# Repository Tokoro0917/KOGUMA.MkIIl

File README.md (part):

# KOGUMA MkIIl

STM32F446RE をベースにしたマイクロマウス(クラシック、迷路探索ロボット)のファームウェア。

- 大会までの予定とやることは`TODO.md`
- 詳しい設計・調べたこと・変更の記録は`docs/`(下の「資料」)

## 目次

1. [動かし方](#動かし方)
2. [大会での流れ](#大会での流れ)
3. [モード](#モード)
4. [出力とビューア](#出力とビューア)
5. [よく変える設定](#よく変える設定)
6. [実機での確認状況](#実機での確認状況)
7. [壁センサ・横壁制御・壁切れ](#壁センサ横壁制御壁切れ)
8. [テストとCI](#テストとci)
9. [ビルド・ハードウェア・ディレクトリ](#ビルドハードウェアディレクトリ)
10. [資料](#資料)

## 動かし方

ロータリーエンコーダの`Encorder_mode_out()`(モード)と`Encorder_number_out()`(ナンバー)の組み合わせで動作を選ぶ。どちらも0〜15。

1. モードとナンバーを選ぶ
2. **左前センサに手をかざす**(`Sensor_Enter()`、FLが1400超)
3. ブザーのあと**左右の横センサに手をかざす**(`Sensor_Start()`、L+Rが2000超)とスタート

走行が終わると`Encorder_count_reset()`でモード0・No.0に戻る。迷路とログはRAMにしか残らないので、**出力するまで電源を切らない**。

## 大会での流れ

大会の日はコードを変えず、感度合わせの値だけ変える(2026-11-21 全日本学生大会の時点)。

1. **ゴールを確かめる**: `Core/Inc/Define.h` の `MAZE_GOOL_X/Y` が `(MAZE_SIZE / 2 - 1)` になっているか(ベンチテストで書き換えたままだとゴールに行けない)
2. **電池**: 満充電で、走る前の電圧が 15.8V 以上
3. **会場に着いたら感度合わせ**(モード3 No.5): 区画中心で値を測る → 出た行(`WallDist_Scale`と各しきい値)を書き写す → ビルドし直して書き込む(手順は「会場ごとの感度合わせ」)。書き込むだけなら STM32CubeIDE の Run(緑の▶)
4. **動作確認**: モード4 No.0(センサ表示)で壁のあり・なし。試走できれば探索して、出力(モード4 No.7)で迷路を見る
5. **探索 → 最短**: モード0 **No.10**(未知壁探索 → スタートに戻る → 2000 の最短)。最短を何回も走れるなら **No.11**(最短4回、最後にスタートへ戻る)。どちらも 2026-11-10 に実機で確認
6. **最短だけ走らせ直す**: モード1 **No.5**(ダイクストラ、コーナー2000、柱の壁切れ。2026-10-25 の九州地区大会で 2.982 秒、優勝)。2400 は V90 を直していないので使わない
7. 走らせるたびに、電源を切らずに出力(モード4 No.7)し、ビューアで保存する(迷路とログはRAMにしか残らない。リセットや電源断で消える)

気をつけること:

- `Core/Inc/Define.h`の`MAZE_GOOL_X/Y`は標準ゴール(迷路中央2×2、`MAZE_SIZE/2-1`)。ベンチテストでスタート近くにゴールを置きたいときだけ一時的に書き換え、**書き換えたままコミットしないこと。** 行き止まり潰しのゴール保護もこの定数から導出している。出力(モード4 No.7)の迷路の図の`G`でゴールの位置を確認できる。
- `Move.c`の`Short_Dijkstra_Move2000()`終端の旋回角度(180°→270°)の調整は、手元で作業中ならリポジトリには未反映。
- **フェイルセーフで止まったとき**(2026-10-27 から、ToraNeko.Mk3 と同じ戻り方): モーターと吸引が止まり、LED が全部 0.5 秒ごとに点滅する。**スイッチ(基板の S2)を押す**と、「ロード中」(LED1〜8 を順に点ける、約1秒)を出してモード0・No.0 に戻る。電源は切らなくてよい。探索中なら、最後に壁を書いた5区画を書く前の状態に戻して保存してあるので、そのまま探索のやり直しや最短走行ができる
- ゴールは1マス(`MAZE_GOOL_X/Y`、16×16で(7,7))を目指して探索する。標準の中央2×2のゴールなら必ず入れるが、そのマスに行けない迷路では探索の逃げ道がなく、前の壁に向かって進んでしまう(全面探索には「どこにも行けなければスタートへ戻る」逃げ道がある)。

## モード

| モード | 内容 | 番号 |
|---|---|---|
| 0 | **大会用: 探索走行**(往復・片道・全面探索・未知壁探索・探索後の最短・最短4回) | No.1〜12 |
| 1 | **最短走行**(BFS / ダイクストラ、コーナー2000・2400・ターンごと。No.12・13は壁切れを従来で。No.14 はきついターン2000・ゆるいターン2400) | No.1〜14 |
| 2 | サーキット(未実装) | |
| 3 | デバッグ: 固定速度の最短(No.1〜3)、距離の表を作る(No.4)、会場ごとの感度合わせ(No.5)、壁切れのテスト(No.6〜9)、吸引のときのセンサのノイズ(No.10) | No.1〜10 |
| 4 | 基本調整: センサ表示、直進、旋回、**出力(No.7)**、最初のターンの調整など | No.0〜14 |
| 5〜9 | 速度別のターン単体テスト(1.0 / 2.0 / 2.4 / 2.7 / 3.0 m/s) | No.0〜7 |
| 10 | ターンごとの通過速度のターン単体テスト | No.1〜7 |

表にない番号(モード0 No.0・No.13〜15、モード1 No.0・No.14〜15、モード2、モード3 No.0・No.11〜15、モード4 No.15、モード10 No.0・No.8〜15、モード11 No.0・No.8〜15、モード12〜15など)は何もしない。

### モード0: 大会用(探索走行)

往路(スタート→ゴール)のあと、片道ならゴールで止まり、それ以外はスタートへ戻る。区間の終わりごとに`Maze_Save()`する。No.8〜10はスタートに戻ったあと2秒待って最短走行(モード1 No.5と同じ: ダイクストラ、コーナー2000、直線6000mm/s、加速20000)まで走る。中身は`main.c`の`Maze_Search(flags)`で、番号ごとに`SEARCH_*`の組み合わせを指定している。

| No | 走り方 | 復路 | `SEARCH_*` |
|---|---|---|---|
| 0 | (何もしない) | | |
| 1 | スラローム探索(500mm/s、吸引なし) | 往復 | `SLALOM` |
| 2 | スラローム探索 | 往復、復路で**エセ全面探索** | `SLALOM \| ALL` |
| 3 | スラローム探索 | **片道**(ゴールで止まる) | `SLALOM \| ONEWAY` |
| 4 | 吸引探索(1000mm/s、吸引あり) | 往復 | `SUCTION` |
| 5 | 吸引探索 | 往復、復路で**エセ全面探索** | `SUCTION \| ALL` |
| 6 | 吸引探索 | ゴール後に**ダイクストラ誘導の未知壁探索**、終わったらスタートへ | `SUCTION \| DIJKSTRA` |
| 7 | 吸引探索+**既知区間加速** | No.6と同じ | `SUCTION \| DIJKSTRA \| KNOWN` |
| 8 | スラローム探索 | 往復 → **最短** | `SLALOM \| SHORTEST` |
| 9 | 吸引探索 | 往復 → **最短** | `SUCTION \| SHORTEST` |
| 10 | 吸引探索+**既知区間加速** | No.6と同じ → **最短** | `SUCTION \| DIJKSTRA \| KNOWN \| SHORTEST` |
| 11 | 吸引探索+**既知区間加速** | No.10 の最短を**4回**。最短のあとは、ゴールから No.6 と同じ探索をしながらスタートへ帰り、2秒待って次の最短。4回目のあともスタートへ帰り、帰れたら曲を流す(自律賞の条件) | `SUCTION \| DIJKSTRA \| KNOWN \| SHORTEST \| REPEAT` |
| 12 | 吸引探索+**既知区間を斜めで**(お遊び、ブランチ `claude/play-known-naname`) | No.10 と同じで、既知区間を斜めの命令列(`Known_Pass_NANAME`)で走る。斜め入り・斜め出・V90 は `G_Turn1000`(モード5で調整)、斜めの直線は最大3000・加速度10000 | `SUCTION \| DIJKSTRA \| KNOWN \| KNOWN_NANAME \| SHORTEST` |

片道(No.3)はゴール区画に入ったところで、Uターンのときと同じ減速(70mm)で止まる。

No.11(2026-10-20)は、最短走行のあと、止まった区画と向きを命令列から求め(`Maze.c`の`Short_Pass_End_Cell()`。ゴールに入った区画の1つ奥の区画の中心で、最後に180°向きを変えている)、そこからスタートへ帰る(`main.c`の`Maze_Return_From_Goal()`)。帰りは、保存した迷路に戻してから(最短走行は見ていない壁を壁で埋めるため)、ダイクストラ誘導の未知壁探索をして、見る壁がなくなったらスタートへ帰る。止まった区画のほかの壁は見ていないことがあるので、最初は来た区画へまっすぐ出る。最短がゴールまで走れなかったときや、帰る途中でフェイルセーフが働いたときは、そこでやめる。走行ログ・壁切れのログは、最後に走った最短のものが残る。

既知区間加速(`Robot_Maze_Pass_Action()`)は、次の区画が探索済みなら、未探索の区画の手前までを`Known_Pass_Generation()`でまとめて経路にし、直線を最大4000mm/sで走る。

ダイクストラ誘導(No.6/No.7/No.10)は往路でゴールに着いたあと、スタート→ゴールのダイクストラ経路上に残っている未確認の壁を、今いる位置から直接見に行く(`Maze_Unknown_Wall_Scan()`)。経路の計算は、未確認の壁を「通れる」として行う。計算し直すのは、ゴールに着いた直後、Uターンしたとき、**見に行った壁が実際にあった・経路のほかの壁が「壁あり」とわかった(経路がふさがれた)とき**、**見に行く途中で目標の区画に行けなくなったとき**(2026-10-27)だけで、どれも**機体が区画の中央で止まっているあいだに**計算する。ゴールに着いた直後と、壁があったときは、次の区画の中央で止まり、前に壁があれば壁合わせをしてから計算し、進む向きを決めて発進する(`Robot_Maze_Stop_And_Go()`)。Uターンでは止まっているあいだに計算し(`G_Stop_Hook`)、行き止まりでなければ計算した結果で進む向きを決め直す。見に行った壁がなかった(通れた)ときは、ダイクストラは計算し直さず、止まらずに同じ経路で次の未確認の壁を探す。経路上の未知壁がなくなったらスタートへ帰る。このとき、その経路の壁はすべて確認済みなので、それが本当の最短経路になる。経路は、よく使う最短走行の値の組(`ShortParam.c` の `G_Short_Run_Set`。今は 2000 と 2400)ごとに、それぞれの時間で一番速いものを求め、全部の組の経路の壁を確認する(2026-10-27。1つ目の組の経路を見終わったら、止まって次の組の経路を計算する)。なので、どの組で最短を走っても本当の最短経路になる。

エセ全面探索(`Maze_Unkown_ALL_ModeSet()`)が有効なのは**No.2・No.5だけ**。したがって**行き止まり潰しが走行に影響するのもこの2つだけ**(`Maze_DeadEnd_Fill()`自体は常に計算されるが、結果を使う`Maze_Gool_Setting()`の分岐がALL_MODE時にしか通らないため)。

探索のアルゴリズム(BFS・ダイクストラ、行き止まり潰し)は`docs/maze_algorithm.md`。

### モード1: 最短走行

`Short_*_Move*(MAX, AC)`の`MAX`が直線区間の最高速度、`AC`が加速度。関数名の数字はコーナー通過速度。直線最高速はどれも6000mm/s。中身は`main.c`の`Maze_Shortest_Run()`。斜めの直線の加速度は番号ごとの`ac_nn`(`G_Short_AC_NANAME`)で決める。

| No | 経路生成 | コーナー | 加速度 | 斜めの加速度 | 関数 |
|---|---|---|---|---|---|
| 0 | (何もしない) | | | | |
| 1 | BFS | 2000 | 15000 | 10000 | `Short_NANAME_Move2000` |
| 2 | BFS | 2000 | 20000 | 15000 | `Short_NANAME_Move2000` |
| 3 | BFS | 2400 | 20000 | 15000 | `Short_NANAME_Move2400` |
| 4 | ダイクストラ | 2000 | 15000 | 10000 | `Short_Dijkstra_Move2000` |
| 5 | ダイクストラ | 2000 | 20000 | 15000 | `Short_Dijkstra_Move2000` |
| 6 | ダイクストラ | 2000 | 23000 | 18000 | `Short_Dijkstra_Move2000` |
| 7 | ダイクストラ | 2000 | 25000 | 20000 | `Short_Dijkstra_Move2000` |
| 8 | ダイクストラ | 2400 | 20000 | 15000 | `Short_Dijkstra_Move2400` |
| 9 | ダイクストラ | 2400 | 23000 | 18000 | `Short_Dijkstra_Move2400` |
| 10 | BFS | ターンごと(`docs/turnv_design.md`) | 20000 | 15000 | `Short_NANAME_MoveTurnV` |
| 11 | ダイクストラ | ターンごと(`docs/turnv_design.md`) | 20000 | 15000 | `Short_Dijkstra_MoveTurnV` |
| 12 | ダイクストラ | 2400(No.8と同じ。**壁切れは従来**、柱と比べる用) | 20000 | 15000 | `Short_Dijkstra_Move2400` |
| 13 | ダイクストラ | 2000(No.5と同じ。**壁切れは従来**、柱と比べる用) | 20000 | 15000 | `Short_Dijkstra_Move2000` |
| 14 | ダイクストラ(経路は No.5 と同じ) | **きついターン(斜め入り45・135、斜め出135、V90)は 2000(`G_Turn2000`)、ゆるいターン(大回り90・大回り180・斜め出45)は 2400(`G_Turn2400`)**。どちらも合わせてある値をそのまま使う。直線を挟まずにつながるターンは 2000 にそろえる。吸引70(2400 と同じ)。2026-11-21、実機では未確認 | 20000 | 15000 | `Short_Dijkstra_MoveMix` |

`main.c`の`Short_WallCut_Pillar`を1にすると、最短走行(モード1、モード0 No.8〜10の探索後の最短)の壁切れを柱で見る(「壁切れ」)。既定は1(2026-10-18 から。0 で従来に戻る)。

No.10・No.11(ターンごとの通過速度)の考え方と速度の決め方は`docs/turnv_design.md`。

No.2とNo.5はパラメータが同一で、BFS経路とダイクストラ経路の比較用になっている。

`Short_Dijkstra_Move2400`は、経路の作り方だけをダイクストラに切り替えて`Short_NANAME_Move2400`と同じ動きで走る(命令列の形はBFSと同じ)。`Short_Dijkstra_Move2000`は旋回のパラメータが`Short_NANAME_Move2000`とは別に調整されている。

コーナー2700(`Short_NANAME_Move2700`)の関数は残してあるが、今はどの番号からも呼んでいない(実機で走れていない)。

### モード3: デバッグ

直線最高速をコーナー速度と同値にして、区間ごとの加減速を実質なくしたもの。

| No | コーナー | 直線最高速 | 加速度 |
|---|---|---|---|
| 1 | 2000 | 2000 | 20000 |
| 2 | 2400 | 2400 | 20000 |
| 3 | 2700 | 2700 | 20000 |
| 4 | 壁センサの距離の表を作る(「距離の表を作り直すとき」) | | |
| 5 | 会場ごとの感度合わせ(区画中心、「会場ごとの感度合わせ」) | | |
| 6〜9 | 壁切れの位置のテスト(500 / 1000 / 2000 / 2400。「壁切れ」、結果は出力 モード4 No.7) | | |
| 10 | 吸引のときのセンサのノイズ(止まったまま約15秒。`docs/sensor_noise.md`) | | |

### モード4: 基本調整

| No | 内容 |
|---|---|
| 0 | センサ値・電圧・ジャイロのprintf表示 |
| 1 | 直進テスト(タイヤ径の測定用。吸引35(探索と同じ、2026-10-21 から。それまでは70)、最大1000・加速度5000で1080mm。タイヤ径 = 今の値 × 実際の距離 / 走行ログの最後の x(1080 より少し手前で止まるので、1080 で割らない)) |
| 2 | その場180°旋回テスト |
| 3 | スラロームテスト |
| 4 | 斜め走行テスト |
| 5 | 吸引ON(duty 90)。左前センサに手をかざすと止まる |
| 6 | 壁合わせ |
| 7 | **出力**。RAMに残っているデータを全部出す(迷路、壁切れのログ、走行ログ。下の「出力とビューア」) |
| 8 | No.1と同じ直進テスト(吸引70、最大1000・加速度5000で1440mm)を、横壁制御のセンサ値版(`Kp`/`Kd`)で走る。距離版との比較・切り戻し用 |
| 9 | 最短走行の最初のターンの調整: 右大回り90を1480で(スタート位置から、ターン後は2400へ加速して1区画で止まる) |
| 10 | 同 右斜め入り45を1110で(ターン後は斜めに2区間で止まる) |
| 11 | 同 右斜め入り135を1400で |
| 12〜14 | No.9〜11 と同じターンを、加速しながら曲がる方式で(`G_First_Turn_Accel = 1`) |

### モード5〜9: 速度別のターン単体テスト

モード5=1.0, 6=2.0, 7=2.4, 8=2.7, 9=3.0 m/s。No.1〜7は共通で 1=90°, 2=180°, 3=in45°, 4=in135°, 5=out45°, 6=out135°, 7=V90°。

| モード | No.0 | No.1〜7 |
|---|---|---|
| 5 (1.0m/s) | 90°小回り(吸引探索の小回り) | 1000のターン単体(`G_Turn1000`、左旋回、壁切れなし。吸引35。置き方は2000と同じ。吸引探索の既知区間の斜め(モード0 No.12)と同じ値。2026-10-21) |
| 6 (2.0m/s) | 直進(吸引51、最大6000・加速度40000で1080mm) | 2000のターン単体(`G_Turn2000`、左旋回、壁切れなし。最短の2000と同じ値) |
| 7 (2.4m/s) | 空 | 2400のターン単体(`G_Turn2400`、左旋回、壁切れなし。最短の2400と同じ値。2026-10-21 から1つずつ単体で走る。斜めから入るターンは斜め3区間で加速するので、2000より斜め2区間ぶん後ろに置く) |
| 8 (2.7m/s) | 空 | 実装済み |
| 9 (3.0m/s) | 空 | **No.1のみ実装**、2〜7は空 |

「空」はセンサ待機だけで何も走らせない分岐。

### モード11: 2200のターンの停止位置テスト(2026-10-20)

[Turn-Sim_KOGUMA](https://tokoro0917.github.io/Turn-Sim_KOGUMA/)(ターンのシミュレーター)の手順3・6・7の「停止位置テスト」。`Move.c` の `G_Turn2200`(シミュレーターの「Cの表をコピー」をそのまま貼る)の値で、ターンを1つ(左)走り、後ろの直線で減速して止まる(`Turn2200_Test()`)。後ろの直線は、斜めに出るターン(斜め入り45・135、V90)は 254.6mm(斜め2区間、斜めの壁の中点で止まる)、まっすぐ出るターン(大回り、斜め出)は 180mm(次の区画の中心で止まる)。シミュレーターの手順3の「後ろの直線の長さ」にも同じ値を入れる。壁切れは使わず、後距離と後ろの直線は壁制御を切る。吸引70。止まった位置を、理想の停止位置(理想の出口の線上で後ろの直線の長さだけ進んだ点)からのずれ(前後・横)として測り、シミュレーターに入れる。番号はモード6と同じ。

| No | ターン | 置き方 |
|---|---|---|
| 1 | 大回り90 | スタート区画(後ろの壁に当てる)。2区画先の区画の中心まで(24 + 360mm)で加速し、そこから前距離 |
| 2 | 大回り180 | 同上 |
| 3 | 斜め入り45 | 同上 |
| 4 | 斜め入り135 | 同上 |
| 5 | 斜め出45 | 斜めに置く。斜め2区間(254.6mm)で加速し、そこ(斜めの壁の中点)から前距離 |
| 6 | 斜め出135 | 同上 |
| 7 | V90 | 同上 |

### モード10: ターンごとの通過速度のターン単体テスト

`Short_NANAME_MoveTurnV`の`TurnV_Table`の速度とパラメータで、ターンを1つだけ走る(`Move.c`の`TurnV_Test()`、左旋回)。モード7と同じく壁切れを使わず、前距離・後距離は固定の距離で走る。表の`v`や`offset_st`/`offset_end`を変えたら、ここで1つずつ確かめる。

| No | ターン |
|---|---|
| 1 | 大回り90 |
| 2 | 大回り180 |
| 3 | 斜め入り45 |
| 4 | 斜め入り135 |
| 5 | 斜め出45(斜め入り45で斜めに入り、斜めの直線1区間で表の速度に合わせてから) |
| 6 | 斜め出135(同上) |
| 7 | V90(同上) |

## 出力とビューア

### 出力(モード4 No.7)

RAMに残っているデータを全部、迷路 → 壁切れのログ → 走行ログ → センサのノイズ の順に出す(ないものは出さない。最後に`#DONE`)。出力のモードはこれひとつ(感度合わせ・距離の表は、そのモードで出し続ける)。

| データ | いつ残るか | 中身 |
|---|---|---|
| 迷路(`MAZE`) | 探索の区間の終わりごと(`Maze_Save()`) | 壁・見た壁、最短走行の命令列(BFS・ダイクストラ)、計算時間。詳しくは`docs/maze_algorithm.md`の「迷路の出力」 |
| 壁切れのログ(`EDGE`) | 最短走行のあいだ、壁切れのテスト(モード3 No.6〜9) | 柱の端、前距離・後距離の始めと終わり、テストでは1mmごとの横センサの値。詳しくは`docs/pillar_cut_design.md`の付録 |
| 走行ログ(`LOG`) | 最短走行(4msおき・6.4秒、走り始めから)、ターンや直進のテスト(1msおき・1.6秒) | 走った距離、速度、角速度、角度、横の壁までの距離、横壁制御、横センサ、電圧、電池、動作。詳しくは`docs/log_design.md` |
| 探索の直進の壁切れ(`SCUT`) | 探索(モード0)のあいだ、1区画まっすぐ進むたび | 次の境目の推定と距離から予想した位置の差(dc)、直した量、使った側、直前の行動、区画。ビューアで直前の行動ごとの表とグラフにし、書き写す基準のずれを出す。見出しにジャイロのゼロ点(`gyro_ofs`・`gyro_sd`・`gyro_rej`、測るたびの値 `gyro_try`、読み直した回数 `gyro_torn`) |
| 前壁の読み分かれ(`FWALL`) | 探索(モード0)の判断位置で、前の左右のセンサの片方だけが閾値を超えたとき | 行動の番号、区画と向き、前の左右の値、左右の平均で見たら壁ありか。本当の迷路と比べて、`Front_Wall_Map` を決める(`docs/search_stability_research.md` の「段階2を入れた結果」) |
| センサのノイズ(`NOISE`) | モード3 No.10 | 吸引と読み方ごとの、点灯時・消灯時・差のばらつきの表(生の値は測ったそばから出すだけで、ここでは出ない)。`docs/sensor_noise.md` |

### ビューア(`tools/viewer.html`)

ロボットのUART出力を、そのままグラフ・表・迷路にするページ。Tera Termはいらない。ネットも使わない(外から何も読み込まないので、会場でも使える)。

1. ロボットをUSBシリアルでつなぎ、`tools/viewer.html`をWindowsのChrome(かEdge)で開く(ダブルクリック)。Tera Termは閉じておく(同じCOMポートは1つしか開けない)
2. 「接続」を押してCOMポートを選ぶ(115200)。届いた文字は下のコンソールに出る
3. 「保存先フォルダ」でリポジトリの`logs/`を選ぶと、届いたデータを1つずつファイル(`日時_種類.txt`)にして自動で保存する。そのファイルをコミットすれば、Claudeは元のデータをそのまま読める
4. ロボットでモード4 No.7(出力)を選ぶと、残っているデータ(迷路・壁切れ・走行ログ)が全部届き、左の一覧に種類ごとに増えて、自動で表示される

届く途中でデータが抜けると、迷路がまるごと届かなかったり、走行ログの行が足りなくなったりする。2026-10-18 までは、受け取りの入れ物が255バイトしかなく、グラフを描いているあいだにあふれていた(1MBにして、届き終わってから描くようにした)。迷路が届かなかったときはコンソールに、走行ログの行が足りないときはそのログの上に出るので、もう一度出力する。

| ロボットの出力 | 表示 |
|---|---|
| 走行ログ | 速度・角速度・角度・横の壁までの距離・横壁制御(出力・P項・D項)・誤差・使った壁・横センサ・電圧・電池のグラフ。動作(直線・前距離・ターン・後距離・止まる)で背景を色分けする。横軸は時間か走った距離を選べる。ドラッグで拡大(全部のグラフがそろう)、ダブルクリックか Esc か「拡大を元に戻す」ボタンで元に戻す、指すとその時刻の値と動作。表示している範囲の平均・標準偏差・最小・最大の表(動作で絞れる)。一覧で別のログに印を付けると破線で重ねる |
| 壁切れのテスト(モード3 No.6〜9で走らせたあと) | 横センサの値と距離のグラフ(1mmごと。区画の境目と見つけた柱の端を重ねる。柱のところで値がどう下がるか、`Edge_Min_High`をいくつにするかを見る)。左右・種類ごとの c-border(境目の推定 − 区画の境目)の平均・標準偏差。そのページで読んだテスト全部を速度ごとにまとめた表と、c-border と速度の点のグラフ(左右別)、書き写す`Edge_Off`の行 |
| 最短走行の壁切れ | 柱の端・前距離・後距離・従来の壁切れを距離の軸に並べた図。前距離をどれだけ直したか、どの推定を使ったかの表。後距離が X より早く終わったかの表 |
| 迷路 | 迷路の図(見ていない壁は点線)に最短経路を重ねる(青: ダイクストラ。BFS と違うときはオレンジの破線も。区画の境目の真ん中を結んで角を丸めた線なので、斜めは斜めに、大回りは丸く出る。ボタンで区画の中心を結ぶ線にも切り替えられる)。経路の命令列・計算時間 |
| センサのノイズ(モード3 No.10) | 吸引ごとの点灯時・消灯時・差のばらつきの表と見立て(電気か、LEDの点け方か)、読み方ごとの差のばらつきの表、吸引とばらつきのグラフ。測ったそばから受け取ったときは、生の値(1msごと100回)のグラフと、差とPWMの位置の散布図も |
| 探索の直進の壁切れ・前壁の読み分かれ | 直前の行動ごとの dc の表とグラフ、書き写す `Search_Edge_Ref`、ジャイロのゼロ点。前の左右が分かれたところの表(区画・向き・値・平均で見ると) |
| 感度合わせ(モード3 No.5) | 書き写す行(コピーのボタン付き)。測っているあいだ約1秒ごとに届くが、一覧には増やさず、いちばん新しい値に置き換える(5秒あくと新しい測定)。自動では保存しない(残したいときは「ファイルに保存」) |
| センサの値(モード4 No.0、モード3 No.4) | 一覧のいちばん上の「センサの値(そのまま)」。直近10秒を流れるグラフ(FL・L・R・FR、モード4 No.0は電池と角速度、モード3 No.4は表で変換した距離も)と、今の値。「止める」で止めて見られる。直近60秒をCSVで保存できる。モード4 No.0の値は10回の移動平均(`g_sensor_av10`)なので、1回だけの落ち込みは見えにくい |

- 保存したファイルや、Tera Termのログは「ファイルを開く」かドラッグで読み込める(`tools/sample_output.txt`はロボットなしで見た目を確かめる用の例)
- 「ぜんぶ保存」は、ページを開いてから届いた文字を1つのファイルにする(長くなったら最後の約10MB、約14分ぶんだけ)
- 出力の形: どれも`#BEGIN 種類 項目=値 ...`で始まり`#END 種類`で終わる(`LOG`・`EDGE`・`MAZE`・`CENTER`)。`LOG`は次の行が列名なので、列を増やしてもビューアは直さなくてよい
- ダブルクリックで開いた(`file://`)ままで、USBシリアルもフォルダへの保存も使える(Chromiumで確かめた)。もし使えなければ、`tools`で`python -m http.server`を実行して`http://localhost:8000/viewer.html`を開く

## よく変える設定

| 設定 | 場所 | 今の値 | 内容 |
|---|---|---|---|
| `Short_WallCut_Pillar` | `main.c` | 1 | 1で、最短走行の壁切れを柱で見る(「壁切れ」)。0で従来 |
| `Pillar_X_Scale` / `Pillar_X_Offs` / `Pillar_Wait_Ofs` | `motor.c` | 0.5 / −5 / 25 | 柱のとき、前距離の X を X × Scale + Offs に読み替える(X は従来に合わせて調整した値のため)。境目が見つからないときは 区画中心 + 読み替えた X + 25 まで待つ |
| `Search_WallCut` / `Search_Edge_Ref` / `Search_Edge_Win` / `Search_Corr_Max` | `motor.c` | 1 / 0 / 20 / 10 | 探索の1区画の直進の壁切れ(`docs/search_wallcut_design.md`)。0 使わない、**1 記録だけ(走りは今までどおり)**、2 直す。2 のときは、区画の4割を過ぎたら次の境目の柱の端を探し、dc(推定 − 予想)と基準のずれ `Search_Edge_Ref`(記録で測った dc の中央値)の差を ± 10mm まで直す |
| `Side_Align_Enable` / `Side_Too_Close_mm` | `motor.c` | 0 / 64 | 探索の横壁合わせ(2026-11-11、ToraNeko.Mk3 と同じ)。区画の入口で、横壁制御が使っている横の壁が 64mm(区画のまん中は 84mm)より近ければ、**0 記録だけ**、1 その区画のまん中で止まり、近い側へ 90° 回って前壁合わせをし、元の向きに戻ってから発進する(Uターンのときはしない)。回数といちばん近かった距離は、出力(モード4 No.7)の探索の直進の壁切れ(SCUT)の見出しの `side_n`・`side_min`(ビューアでは同じカードに出る) |
| `Front_Wall_Map` / `Front_Wall_Min_Ratio` | `motor.c` / `Wallsensor.c` | 1 / 0.33 | 迷路に書く前壁。0 今までどおり(左右とも閾値を超えたら壁)、**1 記録だけ**(左右が分かれたときを `FWALL` に残す)、2 左右の平均でも壁ありにする(低いほうも閾値 × 0.33 を超えたとき) |
| `Alignment_TIME` / `Align_Min_Time` / `Align_Still_Time` / `Align_Still_V` | `motor.c` | 0.5 / 0.10 / 0.05 / 10 | 止まったときの前壁合わせ。左右の車輪が `Align_Still_V`[mm/s]未満の状態が `Align_Still_Time`[s]続いたら終わる(`Align_Min_Time` より早くは終わらない、上限 `Alignment_TIME`) |
| `Align_Use_mm` / `Kp_FW_mm` / `Kp_FW_dire_mm` | `Wallsensor.c` | 1 / 1.8 / 1.8 | 止まったときの前壁合わせを、感度合わせした距離で行う(前後は左右の平均が84mm、向きは左右の距離の差が0)。0 で今までの生の値(`FlontWall_Distance` 636、`Kp_FW` / `Kp_FW_dire` 0.1) |
| `Gyro_Deadband` | `lsm6dsr.c` | 0.15 | ジャイロのゼロ点を測れたあとの不感帯[dps](まだなら 0.5)。ゼロ点は `Motor_Setup` のたびに 0.3 秒止まって測る(`Gyro_Calibrate`。ばらつき 1.5 dps 超・平均 5 dps 超なら前の値のまま。吸引を回すとばらつき 4〜5 dps なので、吸引の前に測った値を使う) |
| `G_Heading_Keep` | `motor.c` | 1 | 直線から直線へ続けて走るとき、向きの基準(`Gyro_Sigma_error`)を引き継ぐ。ターン・壁合わせ・後退・止まったあとは 0 から。0 で今までどおり(直線の関数を呼ぶたびに 0。2026-10-21) |
| `Pillar_Short_X` | `motor.c` | 5 | 柱のとき、X がこれより小さい前距離(2400の斜め入り)は曲がる側の境目だけを使い、見つからなければ 区画中心 + X(従来と同じ)で曲がる |
| `ac_nn` | `main.c`(モード1の番号ごと) | 上の表 | 最短走行の斜めの直線の加速度(0なら直線の加速度-5000) |
| `G_WallCtrl_Use_mm` | `Wallsensor.c` | 1 | 横壁制御。1=距離版、0=センサ値版 |
| `Kp_mm` / `Kd_mm` | `Wallsensor.c` | 0.30 / 0.06 | 距離版の横壁制御のゲイン(センサ値版の`Kp`=0.05 / `Kd`=0.01と同じ効き) |
| `WallDist_Scale` | `WallDistance.c` | 0.99, 0.96, 1.00, 1.02 | 会場ごとの倍率(FL, R, L, FR)。モード3 No.5で測る |
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
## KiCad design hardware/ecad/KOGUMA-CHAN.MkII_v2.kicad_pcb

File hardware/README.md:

# hardware

機体のハードウェアのデータ。

- `KOGUMA.Mk3.step` — 次の機体 **KOGUMA Mk3** の 3D(機械)。設計の狙いは `docs/next_robot.md`(今の機体 MkIIl のよくない点)
- `ecad/` — **KOGUMA Mk3** の回路図と基板(KiCad)

## KOGUMA.Mk3.step

| | |
|---|---|
| 形式 | STEP (ISO 10303-21), スキーマ AP214 (`AUTOMOTIVE_DESIGN`) |
| 単位 | mm |
| 大きさ | 約21MB / 421,590行(git 内では約3MB) |
| 書き出し | Autodesk Translation Framework v15.17 経由(ST-DEVELOPER v20.2) |
| 書き出し日 | 2026-11-24 |

アセンブリ一式(部品ごとに分かれている)。ヘッダの author / organization は空。

### 開き方

- **FreeCAD**(無料): File → Open でそのまま開く
- **Fusion 360**: アップロード → STEP として挿入
- 見るだけなら [3D Viewer](https://3dviewer.net/) 等のブラウザのビューアでも開ける(ローカルで読み込む形式のものを使う)

STEP はテキストだが42万行あって差分に意味がないので、`.gitattributes` で `-text -diff`(行末変換なし・差分なし)にしている。

## 部品構成

STEP の部品名(`PRODUCT`)から読めるもの。`(ミラー)` は左右対称の片側。

### 駆動

| 部品 | 備考 |
|---|---|
| 8520モータ | 8.5×20mm のコアレスモータ |
| スパーギアM0.3_T71 / 歯車M0.3T41 / 歯車M0.3T20 | モジュール0.3、歯数 71 / 41 / 20 |
| LF-630(内輪・外輪・保持器・ボール) | フランジ付きベアリング。玉まで作られている |
| ベアリング(D6 d3) | 外径6 / 内径3 |
| モーターマウントv2、エンコーダギアマウント、足回りv2 | |

歯数から考えられる減速比は **41/20 = 2.05** または **71/20 = 3.55**。今の機体は 1.7073 で、`docs/next_robot.md`「2. モーターとギア比」で「2.0 くらいに上げると立ち上がりの角加速度と低い速度の加速が1割ほど上がる」と見積もった値に 2.05 が合う。ただしどれが実際の減速段かは部品名だけでは決まらないので、CAD で確認が必要。

### 吸引

| 部品 | 備考 |
|---|---|
| 吸引モータ、吸引モーター抑え | |
| 吸引ファン(アクリル) | |
| 8520ファン用モーターマウント | |
| 一次スカート | |
| NFP-D0816S | |

### センサ

| 部品 | 備考 |
|---|---|
| センサまとめ ×4 | 4組。ファームの `G_Wall_data[4]`(FL・L・R・FR)と同数 |
| センサホルダ | |
| 3mm砲丸LED ×4、Φ3弾丸型LED | 発光側 |
| 3mm磁石 | エンコーダ(AS5047)用の径方向着磁マグネットと思われる |

`docs/next_robot.md`「5. センサにのるノイズ」「6. センサの感度と向き」で挙げた、アナログとGNDをモータ・吸引の電流経路から離すことと、発光・受光の向きをそろえることが実際に反映されているかは、基板とホルダを見て確認する。

### 基板・電源・その他

| 部品 | 備考 |
|---|---|
| 基板2 v12、基板3 | メイン基板 |
| エンコーダ基板 | 左右 |
| TSSOP14_OSM | 基板上のICパッケージ |
| Lipo 180mAh | `docs/next_robot.md`「1. 電源の内部抵抗」で、電池・コネクタ・配線で合計 0.2〜0.3Ω を目標にしている |
| 底板v2、全体v2 | |
| M3*5mmスペーサー、アルミテーパーM3、ナイロンナットM3紫、ボタンビス3*14、3*6平行ピン | 締結部品 |

## ecad/ — 回路図と基板(KiCad)

次の機体 **KOGUMA Mk3** の基板。KiCad 9.0 のプロジェクトで、回路図1枚(A3)+ 基板。

| ファイル | 中身 |
|---|---|
| `KOGUMA-CHAN.MkII_v2.kicad_sch` | **回路図の元データ**(テキスト。差分が追える) |
| `KOGUMA-CHAN.MkII_v2.kicad_pcb` | **基板の元データ**。外形は約 61.4 × 94.7mm、板厚1.6mm、2層(F.Cu / B.Cu) |
| `KOGUMA-CHAN.MkII_v2.kicad_pro` | プロジェクト設定 |
| `KOGUMA-CHAN.MkII_v2.pdf` | 回路図の PDF(KiCad の Eeschema 書き出し。KiCad がなくても見られる) |
| `KOGUMA-CHAN.MkII.pdf` | 古い版の回路図(2025-11、Print To PDF のラスタ。文字は選択できない) |
| `KOGUMA-CHAN.f3z` | Fusion 360 のアーカイブ(2025-04)。中に23個の `.f3d`。何のモデルかは自動では判別できなかったが、元データなので残してある |
| `fabrication-toolkit-options.json` | 製造データ書き出しプラグインの設定 |
| `gerber/` | ガーバー + ドリルのジョブファイル |
| `dxf/` | 基板外形とエンコーダ基板の DXF(機械CAD側で使う) |

**`gerber/` は古い版**(2025-05、ファイル名が `KOGUMA-CHAN`、`_v2` でない)。今の `kicad_pcb` は 2026-02 更新なので中身が一致しない。**作り直してから発注すること**。

`dxf/基板.dxf` と `dxf/基板v2.dxf` は、KiCad が `#U57fa#U677f.dxf` という形(日本語を `#Uxxxx` でエスケープしたもの)で書き出したものを、読める名前に直した。中身は変えていない。

### 開き方

- **KiCad 9.0 以降**で `KOGUMA-CHAN.MkII_v2.kicad_pro` を開く(回路図・基板の両方が開く)
- 見るだけなら `KOGUMA-CHAN.MkII_v2.pdf`

### 主な部品

回路図の Value から拾ったもの。**ファームウェアと対応している**。

| 役割 | 部品 | 数 | ファーム側 |
|---|---|---|---|
| マイコン | STM32F446RET6U | 1 | `Core/` 一式。Flash 512KB / RAM 128KB |
| IMU | LSM6DSRXTR | 1 | `lsm6dsr.c` |
| エンコーダ | AS5047P-ATSM | 2 | `PL_encoder.c`(左右)。`KOGUMA.Mk3.step` の 3mm磁石がこれ用 |
| モータドライバ | MP6550GG-P | 2 | `motor.c`(左右) |
| 壁センサ(受光) | SFH_229_FA | 4 | `G_Wall_data[4]`(FL・L・R・FR) |
| センサのアンプ | AD8606ARM 6 / OPV332 4 / NJU6080 2 | | `Wallsensor.c`、`adc.c` |
| 3.3V | MIC5219-3.3YM5-TR | 1 | `LIMITBATT` 15.6V / `REFERENCE_V` 16.0V(`Define.h`) |
| 発振子 | CSTNE10M0G52Z000R0(10MHz) | 1 | HSE |
| ブザー | SMT-0540-S-R | 1 | `Buzzer_Enter()`(`UI.c`) |
| LED | 13 | | `LED1`〜`LED8` ほか(`gpio.c`) |
| スイッチ | SSSS810701(スライド)、他2 | | |
| FET | IRLML6402 / IRLML6344TRPBF / 2N7002 | | 吸引・電源系 |
| SWD | Conn_02x03_Odd_Even | 1 | 書き込み |

ほかに 22u・10u・1u・0.1u などのコンデンサ38個、抵抗31個、ダイオード19個。

### 次の機体 Mk3 の基板

これは **次の機体 KOGUMA Mk3 の基板**。`KOGUMA.Mk3.step`(機械側)と同じ機体のもの。

KiCad のプロジェクト名とファイル名は `KOGUMA-CHAN.MkII_v2` のままで、前の機体から引き継いだ名前になっている。中身は Mk3 用。名前を揃えるなら KiCad の「名前を付けて保存」でプロジェクトごと変える(ファイル同士が名前で参照し合っているので、手で1ファイルずつ変えない)。

**マイコンは今の機体と同じ STM32F446RET6U**(Flash 512KB / RAM 128KB)。`docs/next_robot.md`「8. マイコンと RAM」で「RAM の多いマイコンにする」と挙げた点は、この基板では変わっていない。つまり次の機体でも以下はそのまま残る:

- 16×16 で RAM 約115KB / 128KB。**32×32 は入らない**
- 会場ごとの値をフラッシュに保存する場所を決める話も同じ

IMU(LSM6DSR)・エンコーダ(AS5047P×2)・壁センサ(4組)の構成は今の機体と同じなので、**ファームウェアはほぼそのまま動く**見込み。変わるのはピン割り当てで、今の `KOGUMA.MkIIl.ioc` は MkIIl のものなので、Mk3 用に `.ioc` を作り直すか、`gpio.c` などを基板に合わせる必要がある。

### 除外したファイル

KiCad が作るローカル用のファイルは入れていない(`.gitignore` にも追加済み)。

| ファイル | 理由 |
|---|---|
| `~*.kicad_sch.lck` | **PC名とユーザー名が入っていた**(ロックファイル) |
| `*.kicad_prl` | ローカルの表示状態 |
| `fp-info-cache` | キャッシュ |
| `*.kicad_sch-bak` | KiCad の自動バックアップ |
| `*.pro` | KiCad 5 の遺物(2015年のテンプレの残骸) |

`.kicad_pro` と `.kicad_sch` / `.kicad_pcb` 自体には、ローカルパスも個人情報も入っていないことを確認済み。

## 入っていないもの

部品表(BOM)、組立図、Mk3 用のピン割り当て(`.ioc`。今あるのは MkIIl のもの)。

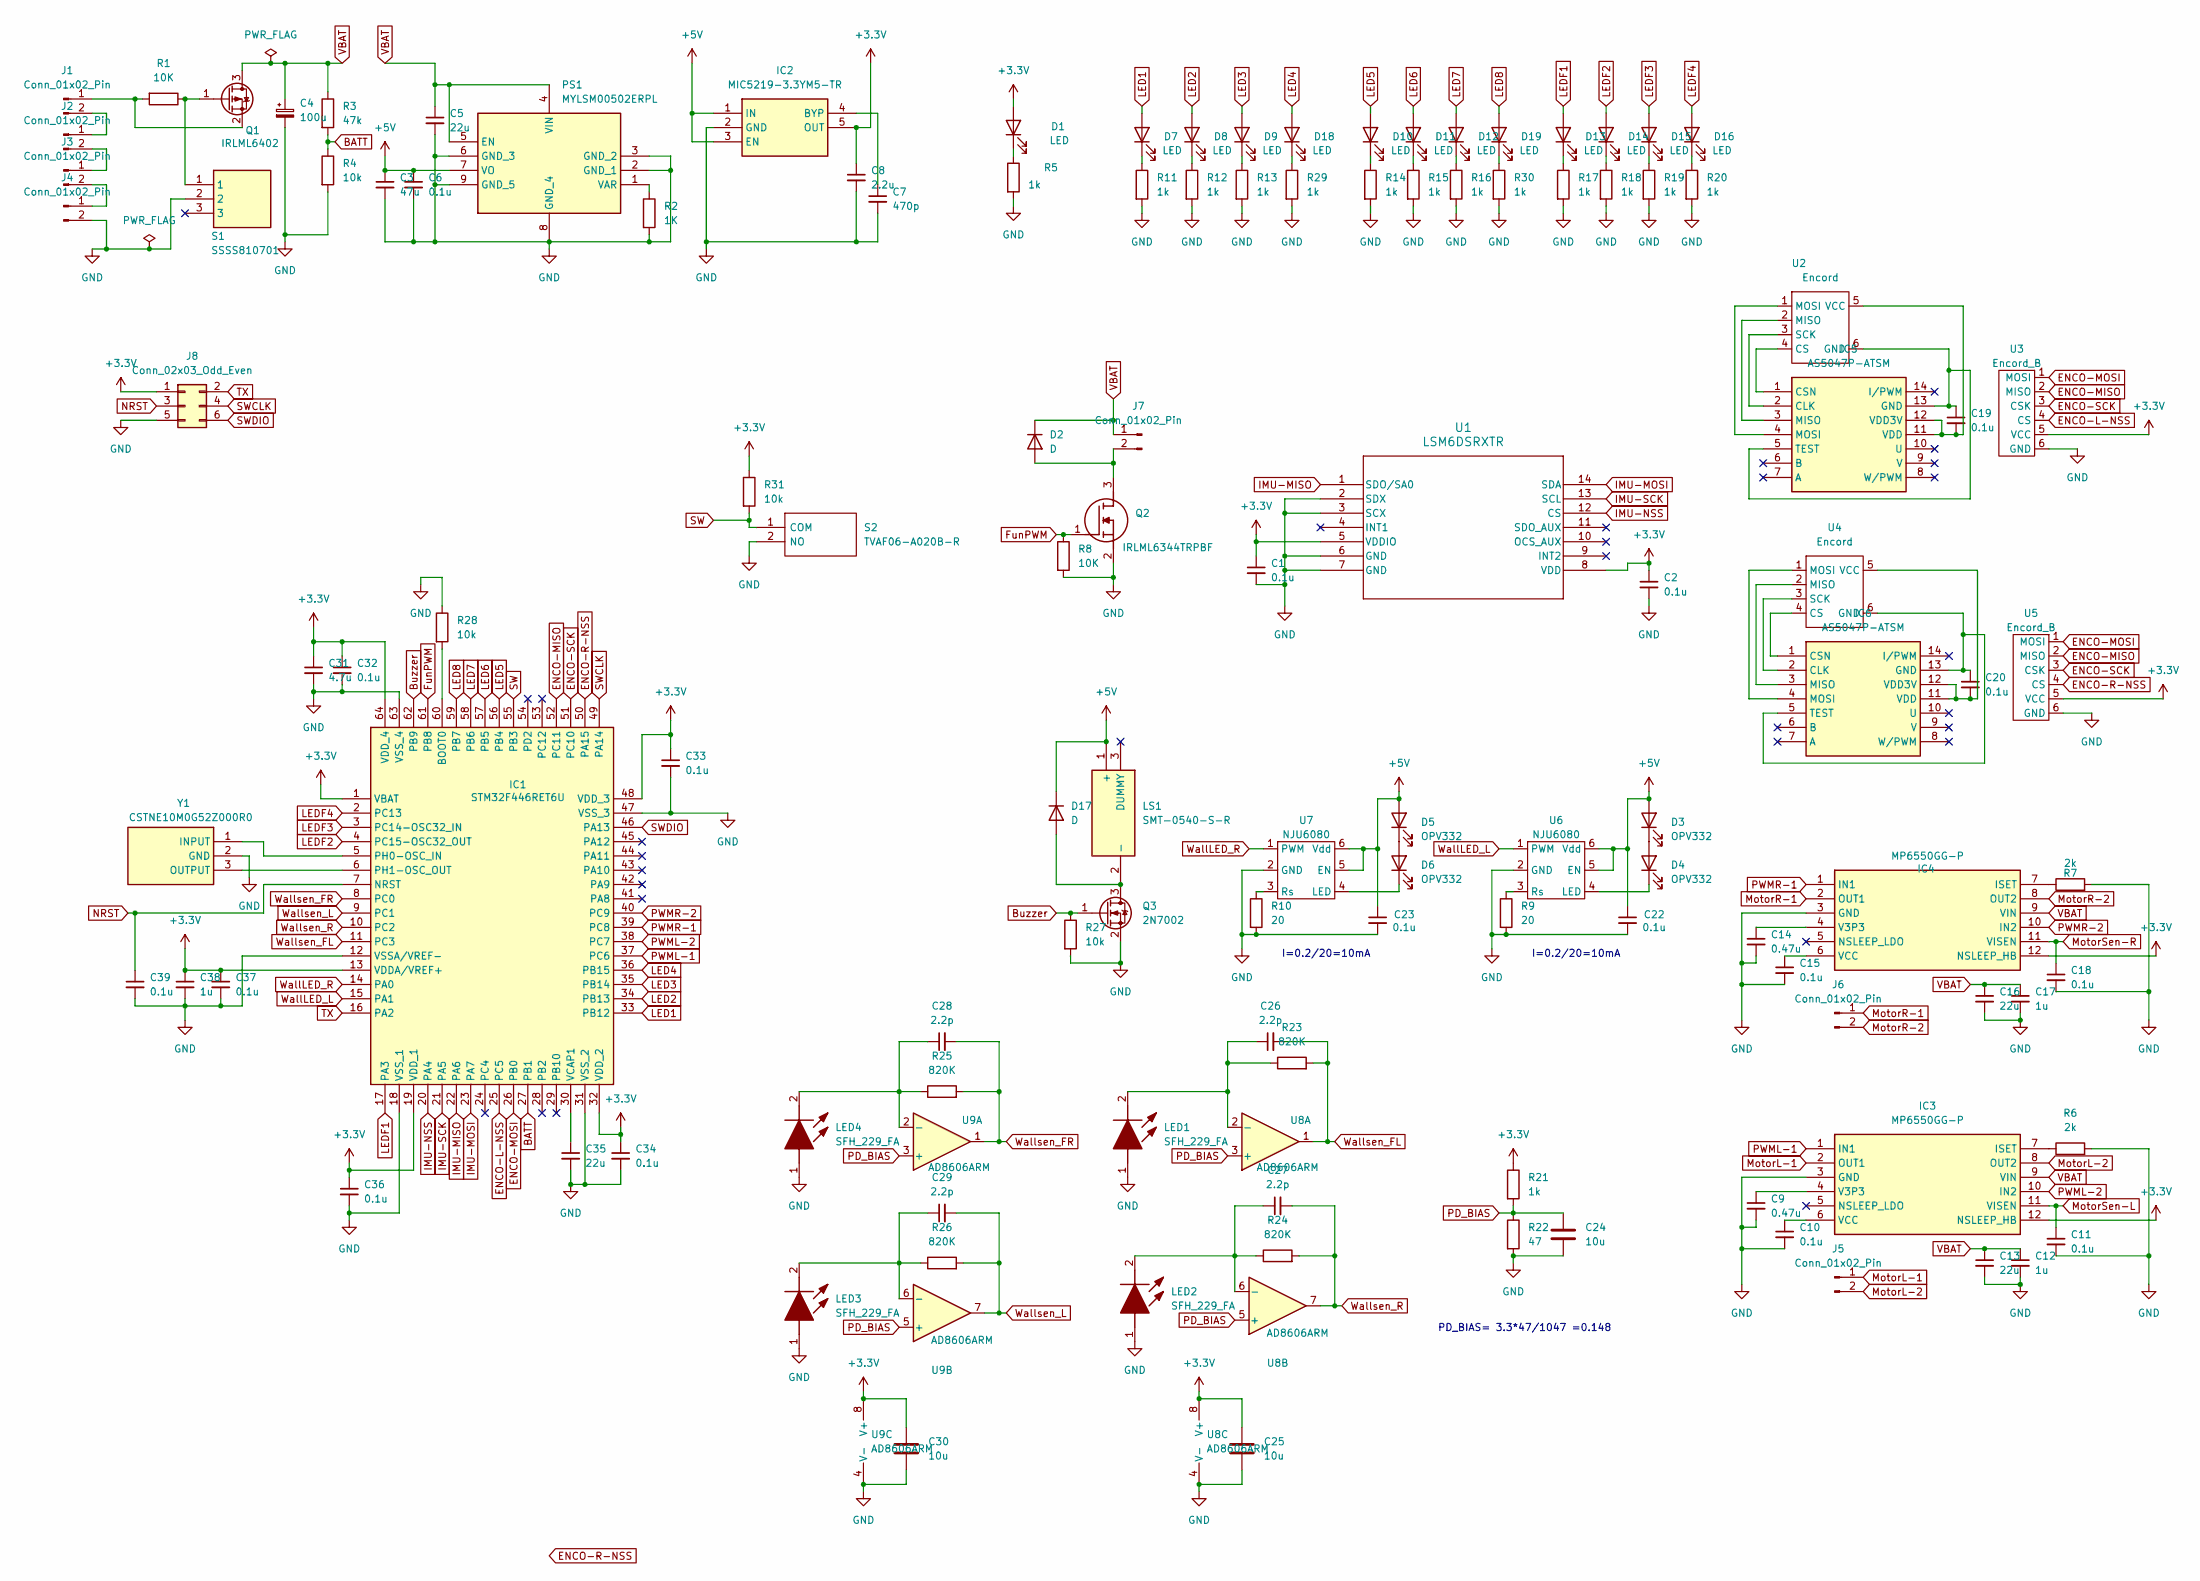
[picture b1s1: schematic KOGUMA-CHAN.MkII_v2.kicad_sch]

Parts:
C1, C2, C6, C10, C11, C15, C18, C19, C20, C22, C23, C32, C33, C34, C36, C37, C39: 0.1u; C_0603_1608Metric
C3: 47u; C_0603_1608Metric
C4: 100u; CP_Elec_6.3x7.7
C5, C13, C16, C35: 22u; C_0805_2012Metric
C7: 470p; C_0603_1608Metric
C8: 2.2u; C_0603_1608Metric
C9, C14: 0.47u; C_0603_1608Metric
C12, C17, C38: 1u; C_0603_1608Metric
C24, C25, C30: 10u; C_0603_1608Metric
C26, C27, C28, C29: 2.2p; C_0603_1608Metric
C31: 4.7u; C_0603_1608Metric
D1, D7, D8, D9, D10, D11, D12, D13, D14, D15, D16, D18, D19: LED; LED_0603_1608Metric
D2, D17: D; D_SOD-123
D3, D4, D5, D6: OPV332; LED_D3.0mm
IC1: STM32F446RET6U; QFP50P1200X1200X160-64N; Manufacturer_Part_Number STM32F446RET6U
IC2: MIC5219-3.3YM5-TR; SOT95P280X145-5N; Manufacturer_Part_Number MIC5219-3.3YM5-TR
IC3, IC4: MP6550GG-P; MP6550GGP; Manufacturer_Part_Number MP6550GG-P
IC5, IC6: AS5047P-ATSM; SOP65P640X120-14N; Manufacturer_Part_Number AS5047P-ATSM
J1, J2, J3, J4, J5, J6, J7: Conn_01x02_Pin; JST_PH_B2B-PH-K_1x02_P2.00mm_Vertical
J8: Conn_02x03_Odd_Even; PinHeader_2x03_P1.27mm_Vertical
LED1, LED2, LED3, LED4: SFH_229_FA; LED_D3.0mm; Manufacturer_Part_Number SFH 229 FA
LS1: SMT-0540-S-R; SMT0540SR; Manufacturer_Part_Number SMT-0540-S-R
PS1: MYLSM00502ERPL; Manufacturer_Part_Number MYLSM00502ERPL
Q1: IRLML6402; SOT-23
Q2: IRLML6344TRPBF; SOT95P237X112-3N; Manufacturer_Part_Number IRLML6344TRPBF
Q3: 2N7002; SOT-23
R1, R8: 10K; R_0603_1608Metric
R2: 1K; R_0603_1608Metric
R3: 47k; R_0603_1608Metric
R4, R27, R28, R31: 10k; R_0603_1608Metric
R5, R11, R12, R13, R14, R15, R16, R17, R18, R19, R20, R21, R29, R30: 1k; R_0603_1608Metric
R6, R7: 2k; R_0603_1608Metric
R9, R10: 20; R_0603_1608Metric
R22: 47; R_0603_1608Metric
R23, R24, R25, R26: 820K; R_0603_1608Metric
S1: SSSS810701; Manufacturer_Part_Number SSSS810701
S2: TVAF06-A020B-R; TVAF06A020BR; Manufacturer_Part_Number TVAF06-A020B-R
U1: LSM6DSRXTR; LGA-14L_STM
U2, U4: Encord; Encoder_EN
U3, U5: Encord_B; Encoder_main
U6, U7: NJU6080; SOT-23-6
U8, U9: AD8606ARM; MSOP-8_3x3mm_P0.65mm
Y1: CSTNE10M0G52Z000R0; Manufacturer_Part_Number CSTNE10M0G52Z000R0

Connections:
+3.3V: C1.1, C2.1, C8.1, C25.1, C30.1, C31.1, C32.1, C33.1, C34.1, C36.1, C37.1, C38.1, D1.2 (A), IC1.1 (VBAT), IC1.13 (VDDA/VREF+), IC1.19 (VDD_1), IC1.32 (VDD_2), IC1.48 (VDD_3), IC1.64 (VDD_4), IC2.5 (OUT), IC3.12 (NSLEEP_HB), IC4.12 (NSLEEP_HB), J8.1, R21.1, R31.1, U1.5 (VDDIO), U1.8 (VDD), U3.5 (VCC), U5.5 (VCC), U8.8 (V+), U9.8 (V+)
+5V: C3.1, C6.1, C22.1, C23.1, D3.2 (A), D5.2 (A), D17.1 (K), IC2.1 (IN), IC2.3 (EN), LS1.1 (+), PS1.7 (VO), U6.5 (EN), U6.6 (Vdd), U7.5 (EN), U7.6 (Vdd)
BATT: IC1.27 (PB1), R3.2, R4.1
Buzzer: IC1.62 (PB9), Q3.1 (G), R27.1
ENCO-L-NSS: IC1.25 (PC5), U3.4 (CS)
ENCO-MISO: IC1.52 (PC11), U3.2 (MISO), U5.2 (MISO)
ENCO-MOSI: IC1.26 (PB0), U3.1 (MOSI), U5.1 (MOSI)
ENCO-R-NSS: IC1.50 (PA15), U5.4 (CS)
ENCO-SCK: IC1.51 (PC10), U3.3 (CSK), U5.3 (CSK)
FunPWM: IC1.61 (PB8), Q2.1 (G), R8.1
GND: C1.2, C2.2, C3.2, C4.2, C5.2, C6.2, C7.2, C8.2, C9.2, C10.2, C11.2, C12.2, C13.2, C14.2, C15.2, C16.2, C17.2, C18.2, C22.2, C23.2, C24.2, C25.2, C30.2, C31.2, C32.2, C33.2, C34.2, C35.2, C36.2, C37.2, C38.2, C39.2, IC1.12 (VSSA/VREF-), IC1.18 (VSS_1), IC1.31 (VSS_2), IC1.47 (VSS_3), IC1.63 (VSS_4), IC2.2 (GND), IC3.3 (GND), IC4.3 (GND), J4.2, J8.5, LED1.1 (A), LED2.1 (A), LED3.1 (A), LED4.1 (A), PS1.2 (GND_1), PS1.3 (GND_2), PS1.6 (GND_3), PS1.8 (GND_4), PS1.9 (GND_5), Q2.2 (S), Q3.2 (S), R2.2, R4.2, R5.2, R6.2, R7.2, R8.2, R9.2, R10.2, R11.2, R12.2, R13.2, R14.2, R15.2, R16.2, R17.2, R18.2, R19.2, R20.2, R22.2, R27.2, R28.1, R29.2, R30.2, S1.2, S2.2 (NO), U1.2 (SDX), U1.3 (SCX)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
IMU-MISO: IC1.22 (PA6), U1.1 (SDO/SA0)
IMU-MOSI: IC1.23 (PA7), U1.14 (SDA)
IMU-NSS: IC1.20 (PA4), U1.12 (CS)
IMU-SCK: IC1.21 (PA5), U1.13 (SCL)
LED1: D7.2 (A), IC1.33 (PB12)
LED2: D8.2 (A), IC1.34 (PB13)
LED3: D9.2 (A), IC1.35 (PB14)
LED4: D18.2 (A), IC1.36 (PB15)
LED5: D10.2 (A), IC1.56 (PB4)
LED6: D11.2 (A), IC1.57 (PB5)
LED7: D12.2 (A), IC1.58 (PB6)
LED8: D19.2 (A), IC1.59 (PB7)
LEDF1: D13.2 (A), IC1.17 (PA3)
LEDF2: D14.2 (A), IC1.4 (PC15-OSC32_OUT)
LEDF3: D15.2 (A), IC1.3 (PC14-OSC32_IN)
LEDF4: D16.2 (A), IC1.2 (PC13)
MotorL-1: IC3.2 (OUT1), J5.1
MotorL-2: IC3.8 (OUT2), J5.2
MotorR-1: IC4.2 (OUT1), J6.1
MotorR-2: IC4.8 (OUT2), J6.2
MotorSen-L: C11.1, IC3.11 (VISEN)
MotorSen-R: C18.1, IC4.11 (VISEN)
NRST: C39.1, IC1.7 (NRST), J8.3
unnamed: D1.1 (K), R5.1
unnamed: D2.2 (A), J7.2, Q2.3 (D)
unnamed: D3.1 (K), D4.2 (A)
unnamed: D4.1 (K), U6.4 (LED)
unnamed: D5.1 (K), D6.2 (A)
unnamed: D6.1 (K), U7.4 (LED)
unnamed: D7.1 (K), R11.1
unnamed: D8.1 (K), R12.1
unnamed: D9.1 (K), R13.1
unnamed: D10.1 (K), R14.1
unnamed: D11.1 (K), R15.1
unnamed: D12.1 (K), R16.1
unnamed: D13.1 (K), R17.1
unnamed: D14.1 (K), R18.1
unnamed: D15.1 (K), R19.1
unnamed: D16.1 (K), R20.1
unnamed: D17.2 (A), LS1.2 (-), Q3.3 (D)
unnamed: D18.1 (K), R29.1
unnamed: D19.1 (K), R30.1
unnamed: IC1.60 (BOOT0), R28.2
unnamed: IC1.5 (PH0-OSC_IN), Y1.1 (INPUT)
unnamed: IC1.6 (PH1-OSC_OUT), Y1.3 (OUTPUT)
unnamed: C35.1, IC1.30 (VCAP1)
unnamed: C7.1, IC2.4 (BYP)
unnamed: IC3.7 (ISET), R6.1
unnamed: C9.1, IC3.4 (V3P3)
unnamed: C10.1, IC3.6 (VCC)
unnamed: IC4.7 (ISET), R7.1
unnamed: C14.1, IC4.4 (V3P3)
unnamed: C15.1, IC4.6 (VCC)
unnamed: IC5.2 (CLK), U2.3 (SCK)
unnamed: IC5.1 (CSN), U2.4 (CS)
unnamed: C19.1, IC5.5 (TEST), IC5.13 (GND), U2.6 (GND)
unnamed: IC5.3 (MISO), U2.2 (MISO)
unnamed: IC5.4 (MOSI), U2.1 (MOSI)
unnamed: C19.2, IC5.11 (VDD), IC5.12 (VDD3V), U2.5 (VCC)
unnamed: IC6.2 (CLK), U4.3 (SCK)
unnamed: IC6.1 (CSN), U4.4 (CS)
unnamed: C20.1, IC6.5 (TEST), IC6.13 (GND), U4.6 (GND)
unnamed: IC6.3 (MISO), U4.2 (MISO)
unnamed: IC6.4 (MOSI), U4.1 (MOSI)
unnamed: C20.2, IC6.11 (VDD), IC6.12 (VDD3V), U4.5 (VCC)
unnamed: J1.1, Q1.2 (S), R1.2
unnamed: J1.2, J2.1
unnamed: J2.2, J3.1
unnamed: J3.2, J4.1
unnamed: C26.1, LED1.2 (K), R23.1, U8.2 (-)
unnamed: C27.1, LED2.2 (K), R24.1, U8.6 (-)
unnamed: C29.1, LED3.2 (K), R26.1, U9.6 (-)
unnamed: C28.1, LED4.2 (K), R25.1, U9.2 (-)
unnamed: PS1.1 (VAR), R2.1
unnamed: Q1.1 (G), R1.1, S1.1
unnamed: R9.1, U6.3 (Rs)
unnamed: R10.1, U7.3 (Rs)
PD_BIAS: C24.1, R21.2, R22.1, U8.3 (+), U8.5 (+), U9.3 (+), U9.5 (+)
PWML-1: IC1.37 (PC6), IC3.1 (IN1)
PWML-2: IC1.38 (PC7), IC3.10 (IN2)
PWMR-1: IC1.39 (PC8), IC4.1 (IN1)
PWMR-2: IC1.40 (PC9), IC4.10 (IN2)
SW: IC1.55 (PB3), R31.2, S2.1 (COM)
SWCLK: IC1.49 (PA14), J8.4
SWDIO: IC1.46 (PA13), J8.6
TX: IC1.16 (PA2), J8.2
VBAT: C4.1, C5.1, C12.1, C13.1, C16.1, C17.1, D2.1 (K), IC3.9 (VIN), IC4.9 (VIN), J7.1, PS1.4 (VIN), PS1.5 (EN), Q1.3 (D), R3.1
WallLED_L: IC1.15 (PA1), U6.1 (PWM)
WallLED_R: IC1.14 (PA0), U7.1 (PWM)
Wallsen_FL: C26.2, IC1.11 (PC3), R23.2, U8.1
Wallsen_FR: C28.2, IC1.8 (PC0), R25.2, U9.1
Wallsen_L: C29.2, IC1.9 (PC1), R26.2, U9.7
Wallsen_R: C27.2, IC1.10 (PC2), R24.2, U8.7

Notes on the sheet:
I=0.2/20=10mA
PD_BIAS= 3.3*47/1047 =0.148

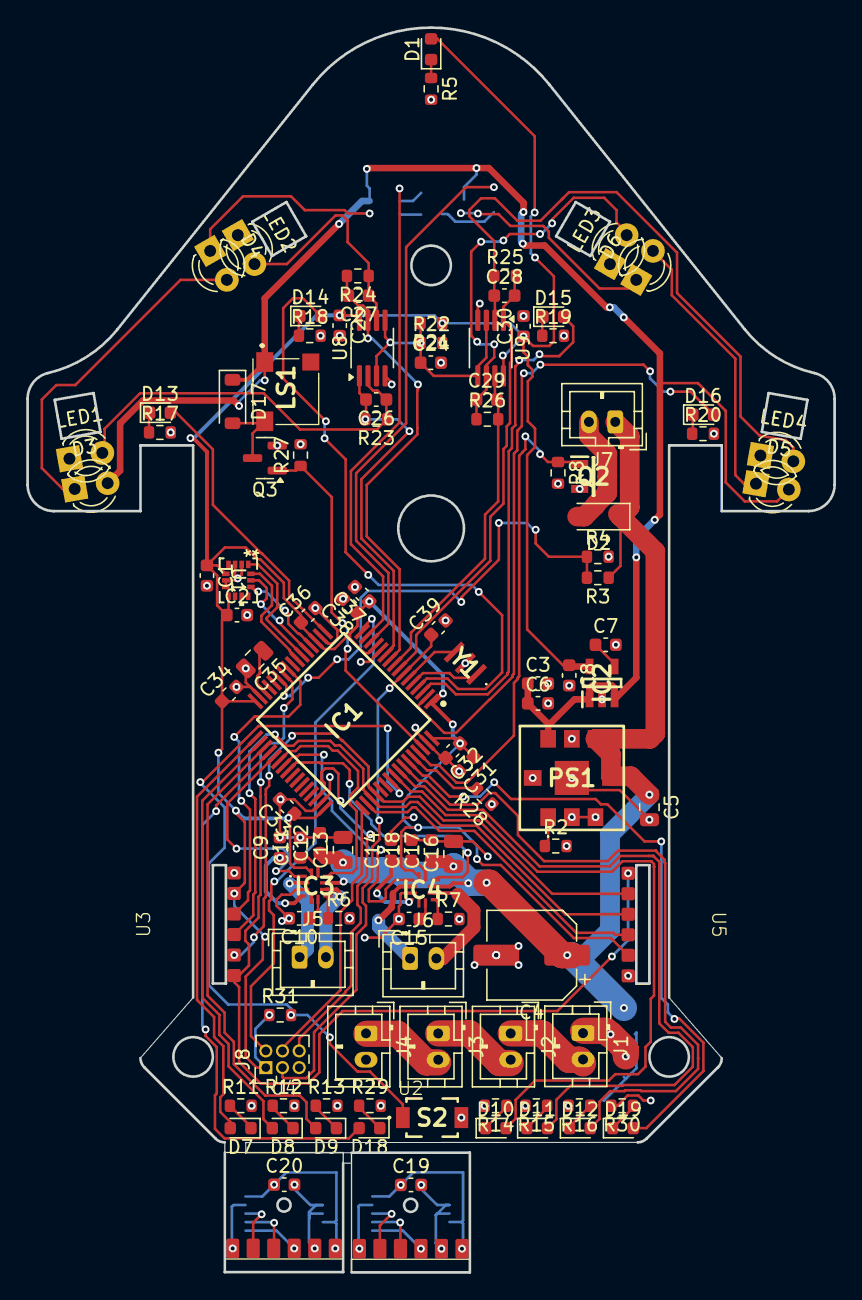
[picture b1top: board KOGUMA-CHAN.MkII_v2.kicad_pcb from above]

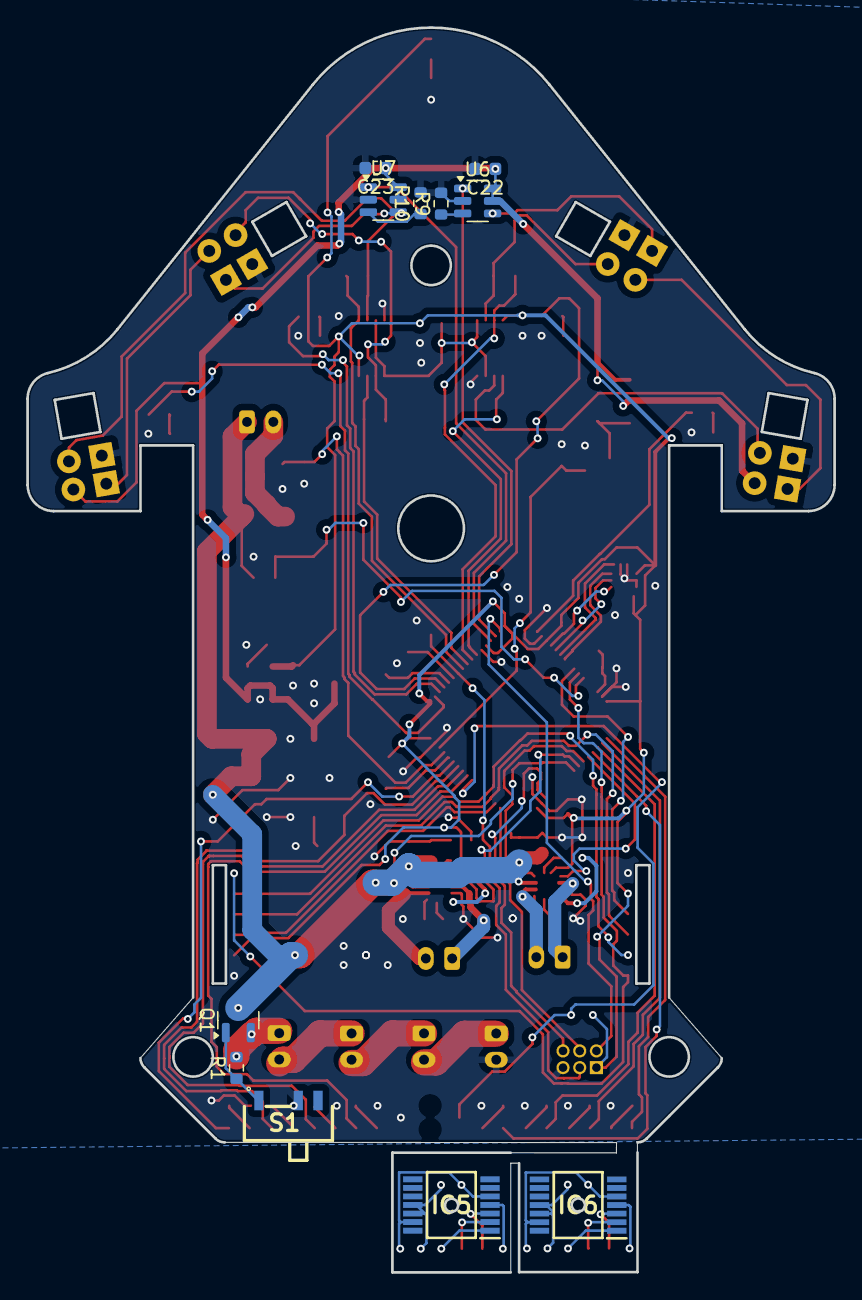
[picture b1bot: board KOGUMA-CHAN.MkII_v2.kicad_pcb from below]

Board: 2 copper layers, 61.4 x 94.7 mm, 123 parts (11 on the bottom side), 104 nets.

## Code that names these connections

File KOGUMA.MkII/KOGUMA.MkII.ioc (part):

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Mcu.Name=STM32F446R(C-E)Tx
Mcu.Package=LQFP64
Mcu.UserName=STM32F446RETx
PA0-WKUP.GPIOParameters=GPIO_Label
PA0-WKUP.GPIO_Label=WallLED_34
PA0-WKUP.Signal=GPIO_Output
PA1.GPIOParameters=GPIO_Label
PA1.GPIO_Label=WallLED_12
PA1.Signal=GPIO_Output
PA10.Signal=GPIO_Output
PA11.Signal=GPIO_Output
PA12.Signal=GPIO_Output
PA13.Signal=SYS_JTMS-SWDIO
PA14.Signal=SYS_JTCK-SWCLK
PA15.GPIOParameters=GPIO_Label
PA15.GPIO_Label=ENCO_R_NSS
PA15.Signal=GPIO_Output
PA2.Mode=Half_duplex(single_wire_mode)
PA2.Signal=USART2_TX
PA3.GPIOParameters=GPIO_Label
PA3.GPIO_Label=LEDF1
PA3.Signal=GPIO_Output
PA4.GPIOParameters=GPIO_Label
PA4.GPIO_Label=ICM_NSS
PA4.Signal=GPIO_Output
PA5.Mode=Full_Duplex_Master
PA5.Signal=SPI1_SCK
PA6.Mode=Full_Duplex_Master
PA6.Signal=SPI1_MISO
PA7.Mode=Full_Duplex_Master
PA7.Signal=SPI1_MOSI
PB0.Mode=Full_Duplex_Master
PB0.Signal=SPI3_MOSI
PB1.Signal=ADCx_IN9
PB12.GPIOParameters=GPIO_Label
PB12.GPIO_Label=LED1
PB12.Signal=GPIO_Output
PB13.GPIOParameters=GPIO_Label
PB13.GPIO_Label=LED2
PB13.Signal=GPIO_Output
PB14.GPIOParameters=GPIO_Label
PB14.GPIO_Label=LED3
PB14.Signal=GPIO_Output
PB4.GPIOParameters=GPIO_Label
PB4.GPIO_Label=LED4
PB4.Signal=GPIO_Output
PB5.GPIOParameters=GPIO_Label
PB5.GPIO_Label=LED5
PB5.Signal=GPIO_Output
PB6.GPIOParameters=GPIO_Label
PB6.GPIO_Label=LED6
PB6.Signal=GPIO_Output
PB8.Signal=S_TIM2_CH1_ETR
PB9.Signal=S_TIM4_CH4
PC0.Signal=ADCx_IN10
PC1.Signal=ADCx_IN11
PC10.Mode=Full_Duplex_Master
PC10.Signal=SPI3_SCK
PC11.Mode=Full_Duplex_Master
PC11.Signal=SPI3_MISO
PC13.GPIOParameters=GPIO_Label
PC13.GPIO_Label=LEDF4
PC13.Signal=GPIO_Output
PC14-OSC32_IN.GPIOParameters=GPIO_Label
PC14-OSC32_IN.GPIO_Label=LEDF3
PC14-OSC32_IN.Signal=GPIO_Output
PC15-OSC32_OUT.GPIOParameters=GPIO_Label
PC15-OSC32_OUT.GPIO_Label=LEDF2
PC15-OSC32_OUT.Signal=GPIO_Output
PC2.Signal=ADCx_IN12
PC3.Signal=ADCx_IN13
PC5.GPIOParameters=GPIO_Label
PC5.GPIO_Label=ENCO_L_NSS
PC5.Signal=GPIO_Output
PC6.Signal=S_TIM3_CH1
PC7.Signal=S_TIM3_CH2
PC8.Signal=S_TIM3_CH3
PC9.Signal=S_TIM3_CH4
PH0-OSC_IN.Mode=HSE-External-Oscillator
PH0-OSC_IN.Signal=RCC_OSC_IN
PH1-OSC_OUT.Mode=HSE-External-Oscillator
PH1-OSC_OUT.Signal=RCC_OSC_OUT
RCC.HSE_VALUE=10000000
RCC.SYSCLKFreq_VALUE=180000000
RCC.SYSCLKSource=RCC_SYSCLKSOURCE_PLLCLK
board=custom

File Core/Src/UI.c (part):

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#include "PL_encoder.h"

void LED_Reset() {
	HAL_GPIO_WritePin(LED1_GPIO_Port, LED1_Pin, 0);
	HAL_GPIO_WritePin(LED2_GPIO_Port, LED2_Pin, 0);
	HAL_GPIO_WritePin(LED3_GPIO_Port, LED3_Pin, 0);
	HAL_GPIO_WritePin(LED4_GPIO_Port, LED4_Pin, 0);
	HAL_GPIO_WritePin(LED5_GPIO_Port, LED5_Pin, 0);
	HAL_GPIO_WritePin(LED6_GPIO_Port, LED6_Pin, 0);
	HAL_GPIO_WritePin(LED7_GPIO_Port, LED7_Pin, 0);
	HAL_GPIO_WritePin(LED8_GPIO_Port, LED8_Pin, 0);
}

void LED_ALL_ON() {
	HAL_GPIO_WritePin(LED1_GPIO_Port, LED1_Pin, 1);
	HAL_GPIO_WritePin(LED2_GPIO_Port, LED2_Pin, 1);
	HAL_GPIO_WritePin(LED3_GPIO_Port, LED3_Pin, 1);
	HAL_GPIO_WritePin(LED4_GPIO_Port, LED4_Pin, 1);
	HAL_GPIO_WritePin(LED5_GPIO_Port, LED5_Pin, 1);
	HAL_GPIO_WritePin(LED6_GPIO_Port, LED6_Pin, 1);
	HAL_GPIO_WritePin(LED7_GPIO_Port, LED7_Pin, 1);
	HAL_GPIO_WritePin(LED8_GPIO_Port, LED8_Pin, 1);
}

/* ロード中(2026-10-27、ToraNeko.Mk3 と同じ)。LED1 から LED8 へ1個ずつ順に点けていき、全部点いたら消す(約1秒)。
 * フェイルセーフを解除してモード選択に戻るときに出す。このあいだは何をしても何も起きない */
void LED_Loading() {
	static GPIO_TypeDef *const port[8] = { LED1_GPIO_Port, LED2_GPIO_Port, LED3_GPIO_Port, LED4_GPIO_Port,
			LED5_GPIO_Port, LED6_GPIO_Port, LED7_GPIO_Port, LED8_GPIO_Port };
	static const uint16_t pin[8] = { LED1_Pin, LED2_Pin, LED3_Pin, LED4_Pin, LED5_Pin, LED6_Pin, LED7_Pin, LED8_Pin };
	LED_Reset();
	for (int i = 0; i < 8; i++) {
		HAL_GPIO_WritePin(port[i], pin[i], 1);
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}

void LED_Setup_Robot() {
	HAL_GPIO_WritePin(LED1_GPIO_Port, LED1_Pin, 0);
	HAL_GPIO_WritePin(LED2_GPIO_Port, LED2_Pin, 0);
	HAL_GPIO_WritePin(LED3_GPIO_Port, LED3_Pin, 0);
	HAL_GPIO_WritePin(LED4_GPIO_Port, LED4_Pin, 0);
	HAL_GPIO_WritePin(LED5_GPIO_Port, LED5_Pin, 0);
	HAL_GPIO_WritePin(LED6_GPIO_Port, LED6_Pin, 0);
	HAL_GPIO_WritePin(LED7_GPIO_Port, LED7_Pin, 0);
	HAL_GPIO_WritePin(LED8_GPIO_Port, LED8_Pin, 0);
	HAL_Delay(100);
	HAL_GPIO_WritePin(LED1_GPIO_Port, LED1_Pin, 1);
	HAL_Delay(100);
	HAL_GPIO_WritePin(LED2_GPIO_Port, LED2_Pin, 1);
	HAL_Delay(100);
	HAL_GPIO_WritePin(LED3_GPIO_Port, LED3_Pin, 1);
	HAL_Delay(100);
	HAL_GPIO_WritePin(LED4_GPIO_Port, LED4_Pin, 1);
	HAL_Delay(100);
	HAL_GPIO_WritePin(LED5_GPIO_Port, LED5_Pin, 1);
	HAL_Delay(100);
	HAL_GPIO_WritePin(LED6_GPIO_Port, LED6_Pin, 1);
	HAL_Delay(100);
	HAL_GPIO_WritePin(LED7_GPIO_Port, LED7_Pin, 1);
	HAL_Delay(100);
	HAL_GPIO_WritePin(LED8_GPIO_Port, LED8_Pin, 1);
	HAL_Delay(200);
	HAL_GPIO_WritePin(LED1_GPIO_Port, LED1_Pin, 0);
	HAL_GPIO_WritePin(LED2_GPIO_Port, LED2_Pin, 0);
	HAL_GPIO_WritePin(LED3_GPIO_Port, LED3_Pin, 0);
	HAL_GPIO_WritePin(LED4_GPIO_Port, LED4_Pin, 0);
	HAL_GPIO_WritePin(LED5_GPIO_Port, LED5_Pin, 0);
	HAL_GPIO_WritePin(LED6_GPIO_Port, LED6_Pin, 0);
	HAL_GPIO_WritePin(LED7_GPIO_Port, LED7_Pin, 0);
	HAL_GPIO_WritePin(LED8_GPIO_Port, LED8_Pin, 0);
}

void LED_batt_error() {
	HAL_GPIO_WritePin(LED1_GPIO_Port, LED1_Pin, 0);
	HAL_GPIO_WritePin(LED2_GPIO_Port, LED2_Pin, 0);
	HAL_GPIO_WritePin(LED3_GPIO_Port, LED3_Pin, 0);
	HAL_GPIO_WritePin(LED4_GPIO_Port, LED4_Pin, 0);
	HAL_GPIO_WritePin(LED5_GPIO_Port, LED5_Pin, 0);
	HAL_GPIO_WritePin(LED6_GPIO_Port, LED6_Pin, 0);
	HAL_GPIO_WritePin(LED7_GPIO_Port, LED7_Pin, 0);
	HAL_GPIO_WritePin(LED8_GPIO_Port, LED8_Pin, 0);
	HAL_Delay(500);
	HAL_GPIO_WritePin(LED1_GPIO_Port, LED1_Pin, 1);
	HAL_GPIO_WritePin(LED2_GPIO_Port, LED2_Pin, 1);
	HAL_GPIO_WritePin(LED3_GPIO_Port, LED3_Pin, 1);
	HAL_GPIO_WritePin(LED4_GPIO_Port, LED4_Pin, 1);
	HAL_GPIO_WritePin(LED5_GPIO_Port, LED5_Pin, 1);
	HAL_GPIO_WritePin(LED6_GPIO_Port, LED6_Pin, 1);
	HAL_GPIO_WritePin(LED7_GPIO_Port, LED7_Pin, 1);
	HAL_GPIO_WritePin(LED8_GPIO_Port, LED8_Pin, 1);
	HAL_Delay(500);
}

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
void LED_Goal() {
	for (int i = 0; i < 2; i++) {
		HAL_GPIO_WritePin(LED1_GPIO_Port, LED1_Pin, 1);
		HAL_GPIO_WritePin(LED2_GPIO_Port, LED2_Pin, 1);
		HAL_GPIO_WritePin(LED3_GPIO_Port, LED3_Pin, 0);
		HAL_GPIO_WritePin(LED4_GPIO_Port, LED4_Pin, 0);
		HAL_GPIO_WritePin(LED5_GPIO_Port, LED5_Pin, 0);
		HAL_GPIO_WritePin(LED7_GPIO_Port, LED7_Pin, 0);
		HAL_GPIO_WritePin(LED8_GPIO_Port, LED8_Pin, 0);
		HAL_Delay(100);
		HAL_GPIO_WritePin(LED1_GPIO_Port, LED1_Pin, 0);
		HAL_GPIO_WritePin(LED2_GPIO_Port, LED2_Pin, 1);
		HAL_GPIO_WritePin(LED3_GPIO_Port, LED3_Pin, 1);
		HAL_GPIO_WritePin(LED4_GPIO_Port, LED4_Pin, 0);
		HAL_GPIO_WritePin(LED5_GPIO_Port, LED5_Pin, 0);
		HAL_GPIO_WritePin(LED7_GPIO_Port, LED7_Pin, 0);
		HAL_GPIO_WritePin(LED8_GPIO_Port, LED8_Pin, 0);
		HAL_Delay(100);
		HAL_GPIO_WritePin(LED1_GPIO_Port, LED1_Pin, 0);
		HAL_GPIO_WritePin(LED2_GPIO_Port, LED2_Pin, 0);
		HAL_GPIO_WritePin(LED3_GPIO_Port, LED3_Pin, 1);
		HAL_GPIO_WritePin(LED4_GPIO_Port, LED4_Pin, 1);
		HAL_GPIO_WritePin(LED5_GPIO_Port, LED5_Pin, 0);
		HAL_GPIO_WritePin(LED7_GPIO_Port, LED7_Pin, 0);
		HAL_GPIO_WritePin(LED8_GPIO_Port, LED8_Pin, 0);
		HAL_Delay(100);
		HAL_GPIO_WritePin(LED1_GPIO_Port, LED1_Pin, 0);
		HAL_GPIO_WritePin(LED2_GPIO_Port, LED2_Pin, 0);
		HAL_GPIO_WritePin(LED3_GPIO_Port, LED3_Pin, 0);
		HAL_GPIO_WritePin(LED4_GPIO_Port, LED4_Pin, 1);
		HAL_GPIO_WritePin(LED5_GPIO_Port, LED5_Pin, 1);
		HAL_GPIO_WritePin(LED7_GPIO_Port, LED7_Pin, 0);
		HAL_GPIO_WritePin(LED8_GPIO_Port, LED8_Pin, 0);
		HAL_Delay(100);
		HAL_GPIO_WritePin(LED1_GPIO_Port, LED1_Pin, 1);
		HAL_GPIO_WritePin(LED2_GPIO_Port, LED2_Pin, 0);
		HAL_GPIO_WritePin(LED3_GPIO_Port, LED3_Pin, 0);
		HAL_GPIO_WritePin(LED4_GPIO_Port, LED4_Pin, 0);
		HAL_GPIO_WritePin(LED5_GPIO_Port, LED5_Pin, 1);
		HAL_GPIO_WritePin(LED7_GPIO_Port, LED7_Pin, 0);
		HAL_GPIO_WritePin(LED8_GPIO_Port, LED8_Pin, 0);
		HAL_Delay(100);
	}
	LED_Reset();
}

void LED_program_number(int N) {
	HAL_GPIO_WritePin(LED5_GPIO_Port, LED5_Pin, 0);
	HAL_GPIO_WritePin(LED6_GPIO_Port, LED6_Pin, 0);
	HAL_GPIO_WritePin(LED7_GPIO_Port, LED7_Pin, 0);
	HAL_GPIO_WritePin(LED8_GPIO_Port, LED8_Pin, 0);
	if (N >= 8) {
		HAL_GPIO_WritePin(LED5_GPIO_Port, LED5_Pin, 1);
		N -= 8;
	}
	if (N >= 4) {
		HAL_GPIO_WritePin(LED6_GPIO_Port, LED6_Pin, 1);
		N -= 4;
	}
	if (N >= 2) {
		HAL_GPIO_WritePin(LED7_GPIO_Port, LED7_Pin, 1);
		N -= 2;
	}
	if (N >= 1) {
		HAL_GPIO_WritePin(LED8_GPIO_Port, LED8_Pin, 1);
	}
}

void LED_program_mode(int N) {
	HAL_GPIO_WritePin(LED1_GPIO_Port, LED1_Pin, 0);
	HAL_GPIO_WritePin(LED2_GPIO_Port, LED2_Pin, 0);
	HAL_GPIO_WritePin(LED3_GPIO_Port, LED3_Pin, 0);
	HAL_GPIO_WritePin(LED4_GPIO_Port, LED4_Pin, 0);
	if (N >= 8) {
		HAL_GPIO_WritePin(LED1_GPIO_Port, LED1_Pin, 1);
		N -= 8;
	}
	if (N >= 4) {
		HAL_GPIO_WritePin(LED2_GPIO_Port, LED2_Pin, 1);
		N -= 4;
	}
	if (N >= 2) {
		HAL_GPIO_WritePin(LED3_GPIO_Port, LED3_Pin, 1);
		N -= 2;
	}
	if (N >= 1) {
		HAL_GPIO_WritePin(LED4_GPIO_Port, LED4_Pin, 1);
	}
}

void LED_ON_R() {
	HAL_GPIO_WritePin(LED7_GPIO_Port, LED7_Pin, 1);
	HAL_GPIO_WritePin(LED8_GPIO_Port, LED8_Pin, 1);
}

void LED_ON_L() {
	HAL_GPIO_WritePin(LED1_GPIO_Port, LED1_Pin, 1);
	HAL_GPIO_WritePin(LED2_GPIO_Port, LED2_Pin, 1);
}

void LED_StartWait() {
	HAL_GPIO_WritePin(LED1_GPIO_Port, LED1_Pin, 0);
	HAL_GPIO_WritePin(LED2_GPIO_Port, LED2_Pin, 1);
	HAL_GPIO_WritePin(LED3_GPIO_Port, LED3_Pin, 0);
	HAL_GPIO_WritePin(LED4_GPIO_Port, LED4_Pin, 1);
	HAL_GPIO_WritePin(LED5_GPIO_Port, LED5_Pin, 0);
	HAL_GPIO_WritePin(LED6_GPIO_Port, LED6_Pin, 1);
	HAL_GPIO_WritePin(LED7_GPIO_Port, LED7_Pin, 0);
	HAL_GPIO_WritePin(LED8_GPIO_Port, LED8_Pin, 1);
	HAL_Delay(200);
	HAL_GPIO_WritePin(LED1_GPIO_Port, LED1_Pin, 1);
	HAL_GPIO_WritePin(LED2_GPIO_Port, LED2_Pin, 0);
	HAL_GPIO_WritePin(LED3_GPIO_Port, LED3_Pin, 1);
	HAL_GPIO_WritePin(LED4_GPIO_Port, LED4_Pin, 0);
	HAL_GPIO_WritePin(LED5_GPIO_Port, LED5_Pin, 1);
	HAL_GPIO_WritePin(LED6_GPIO_Port, LED6_Pin, 0);
	HAL_GPIO_WritePin(LED7_GPIO_Port, LED7_Pin, 1);
	HAL_GPIO_WritePin(LED8_GPIO_Port, LED8_Pin, 0);
	HAL_Delay(200);
}

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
